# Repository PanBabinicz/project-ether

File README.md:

# PROJECT ETHER

## ❓ What is ETHER?

▶️ [Cambridge dictionary:](https://dictionary.cambridge.org/dictionary/english/ether)

> the sky or the air, especially considered as being full of radio waves

▶️ [The fantasy wiki with fictional characters:](https://gods-and-demons.fandom.com/wiki/Aether_(Deity))

> ***"Hi! My name is Aether and I am one of the Protogenoi. I'm the Lord of the stratosphere,
> or as I call it, the Upper Air, Bringer of Light, and the eldest son of Darkness and Night.
> Today, I will be your captain and guide as we explore the strange but fantastic world of Olympus.
> So hold tight to your seatbelts, 'cause this is gonna be one hell of a ride!"***
>
> Aether the god himself is the embodiment of the upper sky, the stratosphere is his domain and 
> with it the air that the gods breathe from. Every world has its own air for its creatures to breathe,
> the underworld is breathed by its monsters, the Human Realm is breathed by its humans, and the Skyland 
> is breathed by the divine beings who control reality; that is the air that Aether controls. It's not just 
> the air of Skyland that he controls however, a portion of the Earth's sky belongs to him as well. The Earthly sky 
> isn't the only cosmic body that Aether can control, the Moon, Stars, Clouds, and partially even the Sun can be controlled by him.

▶️ [The Concept of 'Ether' in Radio Wave Propagation:]

> In the context of radio waves, "ether" refers to the medium through which radio waves propagate.
> This medium is often conceptualized as the space surrounding us, particularly the atmosphere or the open air.
> In the early days of radio communication, scientists believed that radio waves traveled through a substance called
> "ether," filling the space much like air or water fills physical space. While the concept of a physical ether 
> was later debunked by advancements in physics, the term "ether" is still used metaphorically to describe the 
> invisible medium through which radio waves travel.

## ⚒️  Project goal 

> ***The main goal of the project is to create a comprehensive air quality monitoring system, 
> based on the ESP32 platform and integrated with OpenHAB and Grafana. The plan involves the development of 
> a dedicated hardware device equipped with ESP32, appropriate sensors measuring carbon dioxide, temperature, and humidity, 
> as well as a power supply unit. Additionally, the project envisages the use of the MQTT protocol,
> enabling efficient communication between devices, ensuring fast and reliable transmission of sensor data to the server.
> OpenHAB and Grafana will be deployed on the Raspberry Pi platform.***

> [!NOTE]
> **Please bear in mind that the project was primarily created for enjoyment and educational endeavors.**

## Idea Schematic

## 🔌 Hardware

> The hardware for this project was meticulously designed using KiCad, a popular open-source electronic design automation software. 
> The board is a 4-layer design featuring the ESP32-WROOM-32 module at its core. Additionally, it integrates key sensors such as the BME280 and SCD41,
> enabling environmental monitoring capabilities.
>
> The device can be conveniently powered either via USB Type-C connection or an external battery, providing flexibility for different usage scenarios and environments.

## 📖 Software

### Logic Analyzer Output

#### BME280

#### PMS7003

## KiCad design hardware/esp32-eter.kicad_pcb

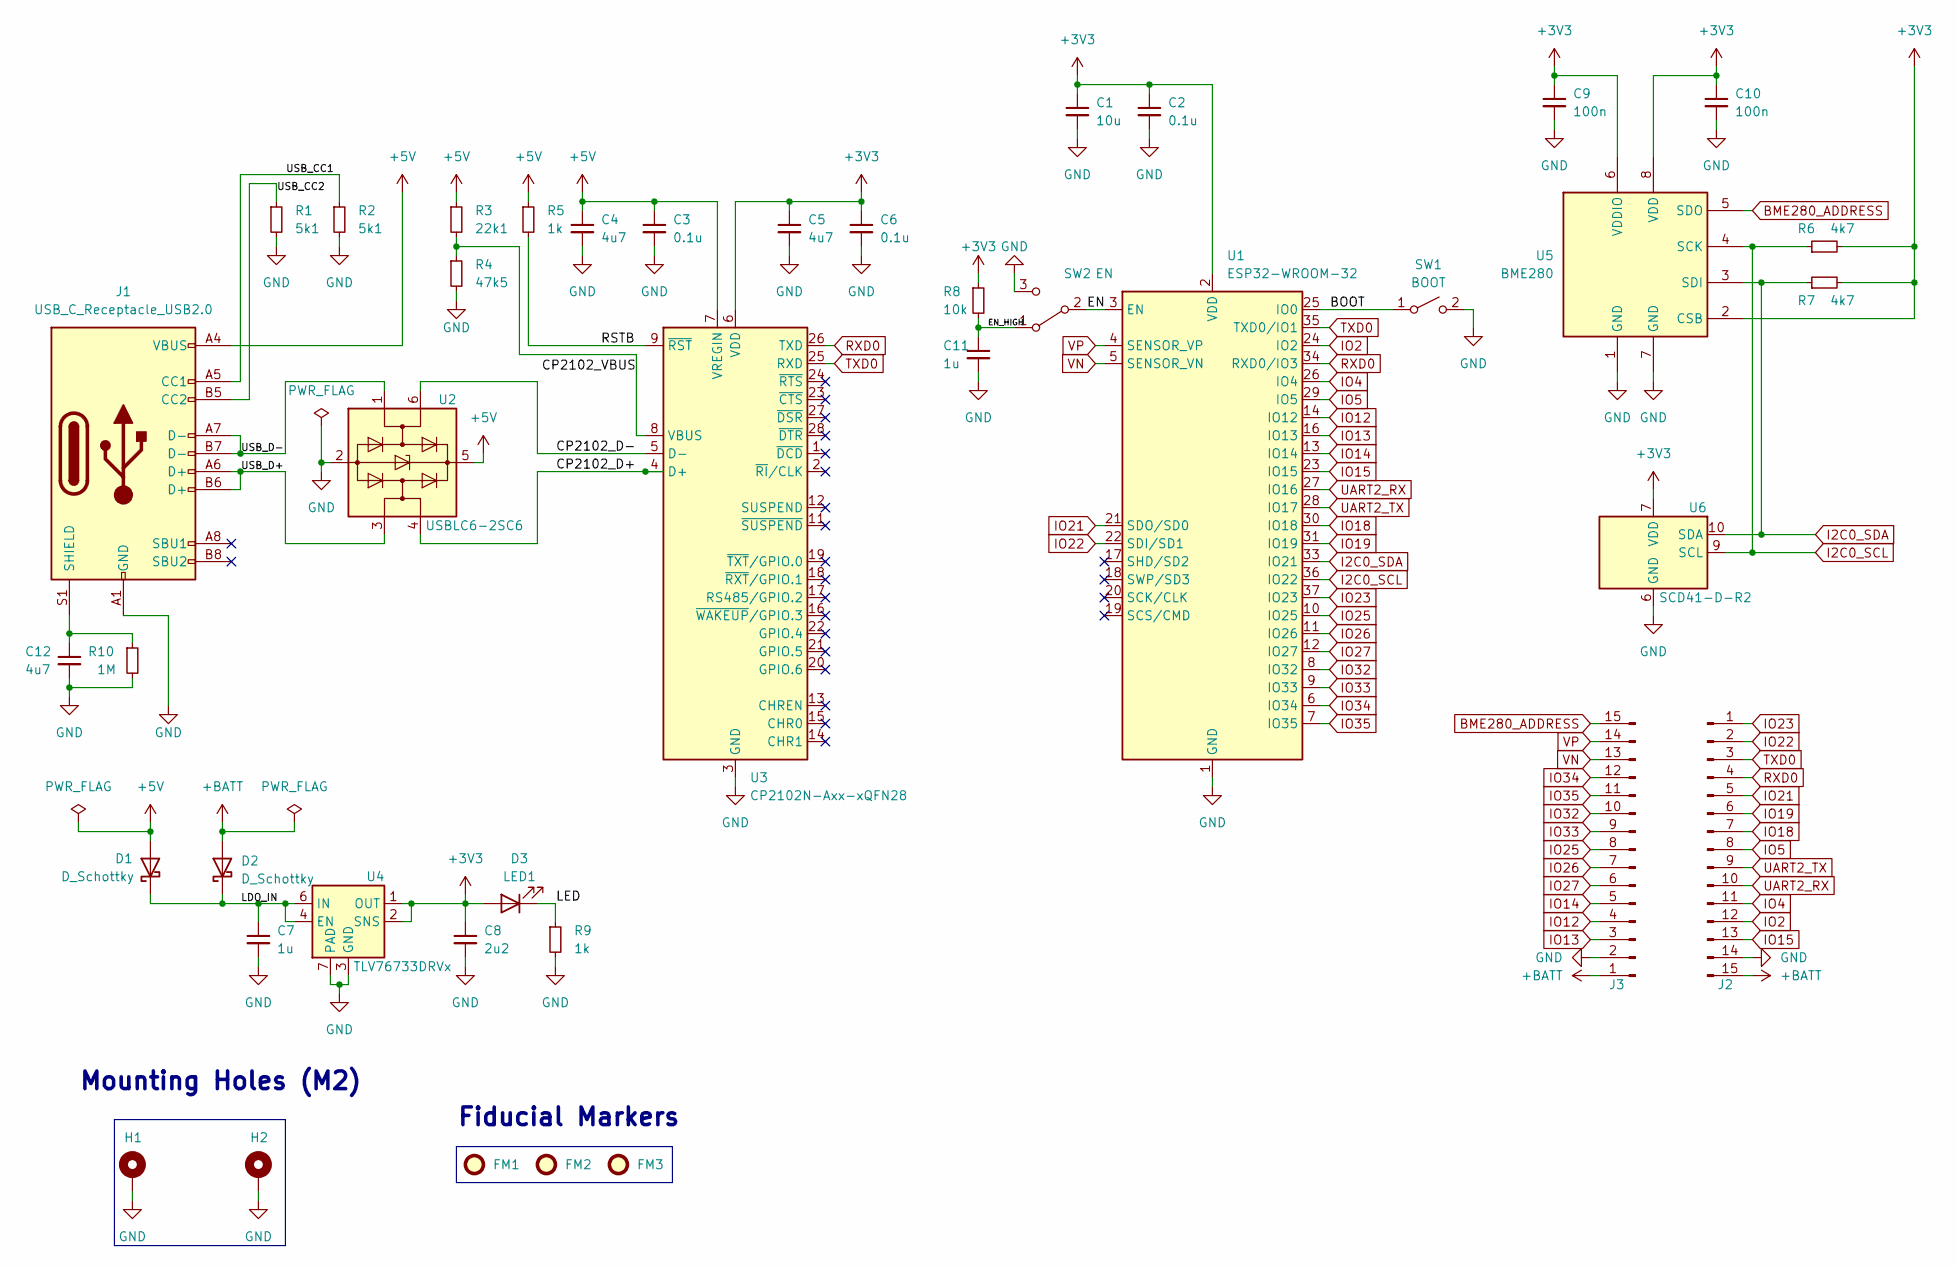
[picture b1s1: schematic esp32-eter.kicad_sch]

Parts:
C1: 10u; C_0805_2012Metric
C2, C3, C6: 0.1u; C_0402_1005Metric
C4, C5, C12: 4u7; C_0603_1608Metric
C7: 1u; C_0805_2012Metric
C8: 2u2; C_0805_2012Metric
C9, C10: 100n; C_0402_1005Metric
C11: 1u; C_0603_1608Metric
D1, D2: D_Schottky; D_0805_2012Metric
D3: LED1; D_1206_3216Metric
FM1, FM2, FM3: Fiducial; Fiducial_1mm_Mask2mm
H1, H2: MountingHole_Pad; MountingHole_2.2mm_M2
J1: USB_C_Receptacle_USB2.0; USB_C_Receptacle_GCT_USB4105-xx-A_16P_TopMnt_Horizontal
J2, J3: Conn_01x15_Pin; PinSocket_1x15_P2.54mm_Vertical
R1, R2: 5k1; R_0402_1005Metric
R3: 22k1; R_0402_1005Metric
R4: 47k5; R_0402_1005Metric
R5, R9: 1k; R_0402_1005Metric
R6, R7: 4k7; R_0402_1005Metric
R8: 10k; R_0402_1005Metric
R10: 1M; R_0603_1608Metric
SW1: BOOT; SW_Push_SPST_NO_Alps_SKRK
SW2: EN; SW_SPDT_CK-JS102011SAQN
U1: ESP32-WROOM-32
U2: USBLC6-2SC6; SOT-23-6
U3: CP2102N-Axx-xQFN28; QFN-28-1EP_5x5mm_P0.5mm_EP3.35x3.35mm
U4: TLV76733DRVx; WSON-6-1EP_2x2mm_P0.65mm_EP1x1.6mm_ThermalVias
U5: BME280; Bosch_LGA-8_2.5x2.5mm_P0.65mm_ClockwisePinNumbering
U6: SCD41-D-R2; Sensirion_SCD4x-1EP_10.1x10.1mm_P1.25mm_EP4.8x4.8mm

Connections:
+3V3: C1.1, C2.1, C5.1, C6.1, C8.1, C9.1, C10.1, D3.2 (A), R6.2, R7.2, R8.1, U1.2 (VDD), U3.6 (VDD), U4.1 (OUT), U4.2 (SNS), U5.2 (CSB), U5.6 (VDDIO), U5.8 (VDD), U6.7 (VDD), U6.19 (VDD)
+5V: C3.1, C4.1, D1.2 (A), J1.A4 (VBUS), J1.A9 (VBUS), J1.B4 (VBUS), J1.B9 (VBUS), R3.1, R5.1, U2.5 (VBUS), U3.7 (VREGIN)
+BATT: D2.2 (A), J2.15, J3.1
/BOOT: SW1.1 (A), U1.25 (IO0)
/CP2102_D+: U2.4 (I/O2), U3.4 (D+)
/CP2102_D-: U2.6 (I/O1), U3.5 (D-)
/CP2102_VBUS: R3.2, R4.1, U3.8 (VBUS)
/EN: SW2.2 (B), U1.3 (EN)
/EN_HIGH: C11.1, R8.2, SW2.1 (A)
/LDO_IN: C7.1, D1.1 (K), D2.1 (K), U4.4 (EN), U4.6 (IN)
/LED: D3.1 (K), R9.1
/RSTB: R5.2, U3.9 (~RST)
/USB_CC1: J1.A5 (CC1), R2.1
/USB_CC2: J1.B5 (CC2), R1.1
/USB_D+: J1.A6 (D+), J1.B6 (D+), U2.3 (I/O2)
/USB_D-: J1.A7 (D-), J1.B7 (D-), U2.1 (I/O1)
BME280_ADDRESS: J3.15, U5.5 (SDO)
GND: C1.2, C2.2, C3.2, C4.2, C5.2, C6.2, C7.2, C8.2, C9.2, C10.2, C11.2, C12.2, H1.1, H2.1, J1.A1 (GND), J1.A12 (GND), J1.B1 (GND), J1.B12 (GND), J2.14, J3.2, R1.2, R2.2, R4.2, R9.2, R10.2, SW1.2 (B), SW2.3 (C), U1.1 (GND), U1.15 (GND), U1.38 (GND), U1.39 (GND), U2.2 (GND), U3.3 (GND), U3.29 (GND), U4.3 (GND), U4.5 (GND), U4.7 (PAD), U5.1 (GND), U5.7 (GND), U6.6 (GND), U6.20 (GND), U6.21 (GND)
I2C0_SCL: R6.1, U1.36 (IO22), U5.4 (SCK), U6.9 (SCL)
I2C0_SDA: R7.1, U1.33 (IO21), U5.3 (SDI), U6.10 (SDA)
IO2: J2.12, U1.24 (IO2)
IO4: J2.11, U1.26 (IO4)
IO5: J2.8, U1.29 (IO5)
IO12: J3.4, U1.14 (IO12)
IO13: J3.3, U1.16 (IO13)
IO14: J3.5, U1.13 (IO14)
IO15: J2.13, U1.23 (IO15)
IO18: J2.7, U1.30 (IO18)
IO19: J2.6, U1.31 (IO19)
IO21: J2.5, U1.21 (SDO/SD0)
IO22: J2.2, U1.22 (SDI/SD1)
IO23: J2.1, U1.37 (IO23)
IO25: J3.8, U1.10 (IO25)
IO26: J3.7, U1.11 (IO26)
IO27: J3.6, U1.12 (IO27)
IO32: J3.10, U1.8 (IO32)
IO33: J3.9, U1.9 (IO33)
IO34: J3.12, U1.6 (IO34)
IO35: J3.11, U1.7 (IO35)
unnamed: C12.1, J1.S1 (SHIELD), R10.1
RXD0: J2.4, U1.34 (RXD0/IO3), U3.26 (TXD)
TXD0: J2.3, U1.35 (TXD0/IO1), U3.25 (RXD)
UART2_RX: J2.10, U1.27 (IO16)
UART2_TX: J2.9, U1.28 (IO17)
VN: J3.13, U1.5 (SENSOR_VN)
VP: J3.14, U1.4 (SENSOR_VP)

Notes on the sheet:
Mounting Holes (M2)
Fiducial Markers

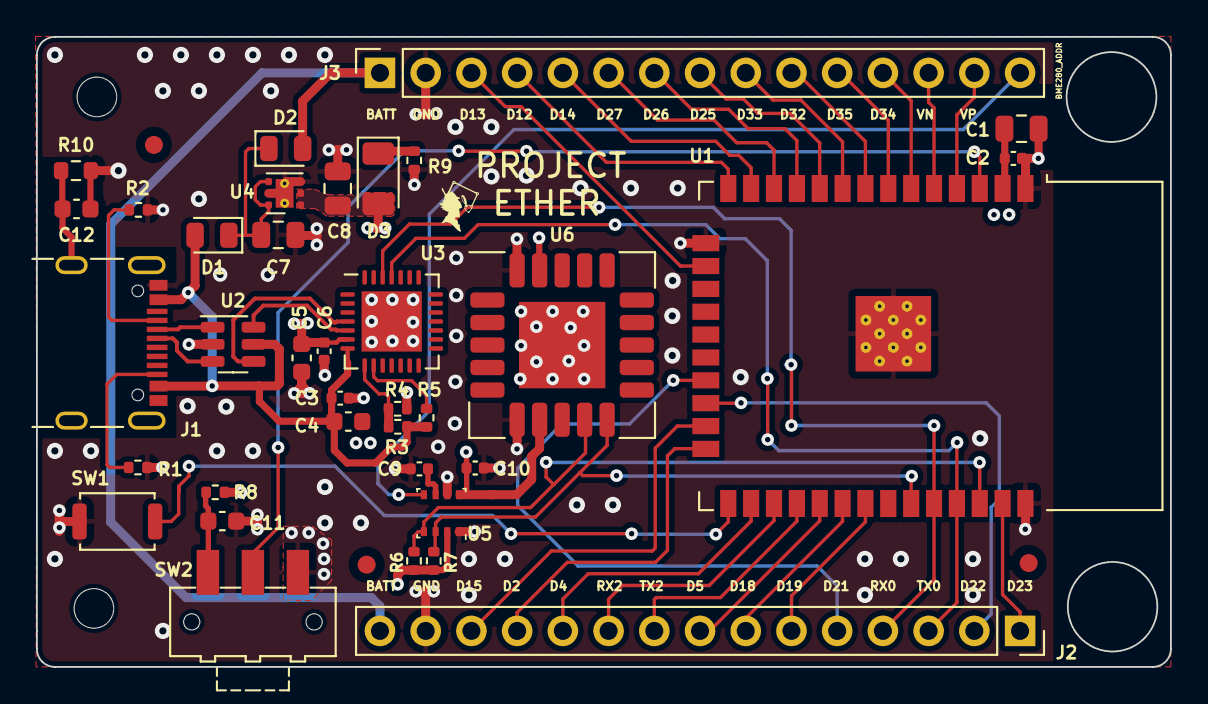
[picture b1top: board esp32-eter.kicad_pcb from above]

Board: 4 copper layers, 63.0 x 35.0 mm, 41 parts (0 on the bottom side), 46 nets.

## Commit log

2024-05-01 PROJECT-ETHER-001: Add current work.
2024-05-01 PROJECT-ETHER-002: Clean manufacturing directory.
2024-05-03 PROJECT-ETHER-MQTT-001: Add submodule.
2024-05-03 PROJECT-ETHER-MQTT-002: Remove mosquitto.
2024-05-03 PROJECT-ETHER-UART-001: Add uart_controller files, combine two sensors in demo.
2024-05-05 PROJECT-ETHER-MQTT-003: Add wifi demo.
2024-05-11 PROJECT-ETHER-MQTT-004: Add MQTT demo.
2024-05-11 PROJECT-ETHER-MAIN: Delete unnecessary files.
2024-05-11 PROJECT-ETHER-MAIN: Delete pytest file.
2024-05-11 PROJECT-ETHER-MAIN: Delete sdk files.
2024-05-12 PROJECT-ETHER-MAIN: Apply new coding style.
2024-05-12 PROJECT-ETHER-MAIN: Correct the doxygen comments.
2024-05-18 PROJECT-ETHER-MAIN: Create new pms7003 task.
2024-05-26 PROJECT-ETHER-MAIN: Create mqtt task for sending data to mqtt broker.
2024-05-26 PROJECT-ETHER-MAIN: Add & to function pointers to make it more readable.
2024-05-26 PROJECT-ETHER-MAIN: Change the resistor value for the led diode.
2024-06-05 PROJECT-ETHER-REFACTOR: Add the state machines for sensors.
2024-06-07 PROJECT-ETHER-REFACTOR: Clean the state machines and add DEBUG.
2024-06-07 PROJECT-ETHER-REFACTOR: Delete unused function from ether_main.
2024-06-07 PROJECT-ETHER-REFACTOR: Fix bme280 state machine transition from reset to init.
2024-06-07 PROJECT-ETHER-REFACTOR: Add title to project README.
2024-06-07 PROJECT-ETHER-REFACTOR: Add goal to project README.
2024-06-07 PROJECT-ETHER-REFACTOR: Check note highlight to project README.
2024-06-07 PROJECT-ETHER-REFACTOR: Add note highlight to project README.
2024-06-07 PROJECT-ETHER-REFACTOR: Add hardware images to project README.
2024-06-07 PROJECT-ETHER-REFACTOR: Check hardware images to project README.
2024-06-07 PROJECT-ETHER-REFACTOR: Check hardware front image to project README.
2024-06-07 PROJECT-ETHER-REFACTOR: Check hardware back image to project README.
2024-06-07 PROJECT-ETHER-REFACTOR: Add hardware description to project README.
2024-06-08 PROJECT-ETHER-REFACTOR: Add ETHER_DEGUB flag check inside bme280 task.
2024-06-08 PROJECT-ETHER-REFACTOR: Add doxygen documentation for BME280 sensor.
2024-06-08 PROJECT-ETHER-REFACTOR: Add doxygen documentation for ETHER system.
2024-06-08 PROJECT-ETHER-REFACTOR: Add doxygen documentation for i2c_controller.
2024-06-08 PROJECT-ETHER-REFACTOR: Add doxygen documentation for mqtt_controller.
2024-06-08 PROJECT-ETHER-REFACTOR: Add doxygen documentation for pms7003 sensor.
2024-06-08 PROJECT-ETHER-REFACTOR: Add doxygen documentation for state_machine.
2024-06-08 PROJECT-ETHER-REFACTOR: Add doxygen documentation for uart and wifi controllers.
2024-06-08 PROJECT-ETHER-REFACTOR: Add simple doxygen documentation.
2024-06-08 PROJECT-ETHER-REFACTOR: Add ether doxygen documentation.
2024-06-08 PROJECT-ETHER-MAIN: Remove blink project README.
2026-04-12 doc: Add screenshots
2026-04-12 doc: Add idea schematic
2026-04-12 doc: Update README.md
